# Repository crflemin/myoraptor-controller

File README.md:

# myoraptor-controller
This is the second iteration (but let's call it version 1.0) of a project combining the Raptor Reloaded 3D printed prosthetic with a MyoWare EMG sensor, a DC motor, and a Teensy 3.2. The goal is to build a prosthetic hand that responds to muscle contractions. I worked on the first iteration with an exceptional high school student who prototyped the design of the electronics control system using an Arduino Uno, breadboard, and wires. Shashi Jain designed the linear rail adapter and inspired us to combine the motor-driven Raptor with the MyoWare sensor. My contribution to this project was in pulling together the great work of these others and creating the PCB to slim down the device into something potentially wearable. I also want to thank <a href="https://github.com/wickerbox/">Wickerbox Electronics</a> for the KiCAD support and library resources!

This repository contains KiCAD design files for a PCB shield for the Teensy 3.2, as well as the Arduino code used to operate the hand.

Visit <a href="http://www.chloefleming.com/?p=90">my website</a> for pictures and more information.

## Components
1 x <a href="http://www.thingiverse.com/thing:596966">Raptor Reloaded</a> hand (scaled to 122%)</br>
1 x <a href="https://tinkercad.com/things/4MtmrpRE7Zj">linear rail adapter</a> for the Raptor Reloaded</br>
1 x <a href="https://www.adafruit.com/product/2699">MyoWare EMG sensor</a></br>
1 x <a href="https://oshpark.com/shared_projects/Pn4XONTR">MyoRaptor Controller PCB</a></br>
1 x DC motor (up to 12V)</br>

## Notes on Version 1.0
Here are some thoughts I have on the current working state of this project, and what should be done to improve future versions: </br>
* I am using a 9V battery to drive this circuit, but I am not convinced that this is moving the motor quickly enough and will likely look into other options.
* The DC motors with sufficient torque tend to be a bit bulky, and attaching them to the Raptor is not easy (this is currently being accomplished with a cheap plastic pipe clamp and a zip tie). A custom printed part should be designed to hold the motor. I'd also like to try to locate a smaller motor to power the hand.
* Right now, the PCB and linear rail adapter are sized to fit in the 122% hand. The linear rail should be made scalable with parameters and the PCB size may also need to be adjusted for smaller hands.
* The current version lacks a neat way to attach the PCB to the inside of the palm of the hand, which is another thing I'd like to improve with a printed part.

## Assembly Instructions
(in progress)

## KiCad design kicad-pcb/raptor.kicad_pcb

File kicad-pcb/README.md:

# myoraptor-controller
A PCB shield for controlling the Raptor Reloaded 3D printed prosthetic with the MyoWare EMG sensor. KiCAD library references point to <a href="https://github.com/wickerbox/">Wickerbox Electronics</a>. 
Click <a href="https://oshpark.com/shared_projects/Pn4XONTR">here</a> to order this board from OSH Park!

## Board Previews
(Courtesy of OSH Park) </br>

## Bill of Materials
|Ref|Quantity|Digikey Part Number|Manufacturer Part Number|Description|
|---|--------|-------------------|------------------------|-----------|
|U2|1|296-9911-5-ND|SN754410NE|IC HALF-H DRVR QUAD 16-DIP|
|J2, J4|2|ED10561-ND|OSTVN02A150|CONN TERM BLOCK 2.54MM 2POS PCB|
|J3|1|OSTVN03A150|OSTVN03A150|CONN TERM BLOCK 2.54MM 3POS PCB|
|D1|1|SMAJ14A-FDICT-ND|SMAJ14A-13-F|TVS DIODE 14VWM 23.2VC SMA|
|U1|1|NCP1117LPST50T3GOSCT-ND|NCP1117LPST50T3G|IC REG LDO 5V 1A SOT223|
|F1|1|MF-MSMF110/24X-2CT-ND|MF-MSMF110/24X-2|FUSE PTC RESET 1.10A SMD 1812|
|D2, D3|2|SS12-E3/61TGICT-ND|SS12-E3/61T|DIODE SCHOTTKY 20V 1A DO214AC|
|C4|1|490-1519-1-ND|GRM188R71H104KA93D|CAP CER 0.1UF 50V X7R 0603|
|C3|1|490-5307-1-ND|GRM188R71E105KA12D|CAP CER 1UF 25V X7R 0603|
|C1, C2|2|490-7202-1-ND|GRM188R61E106MA73D|CAP CER 10UF 25V X5R 0603|
|J1|1|||Teensy 3.2|

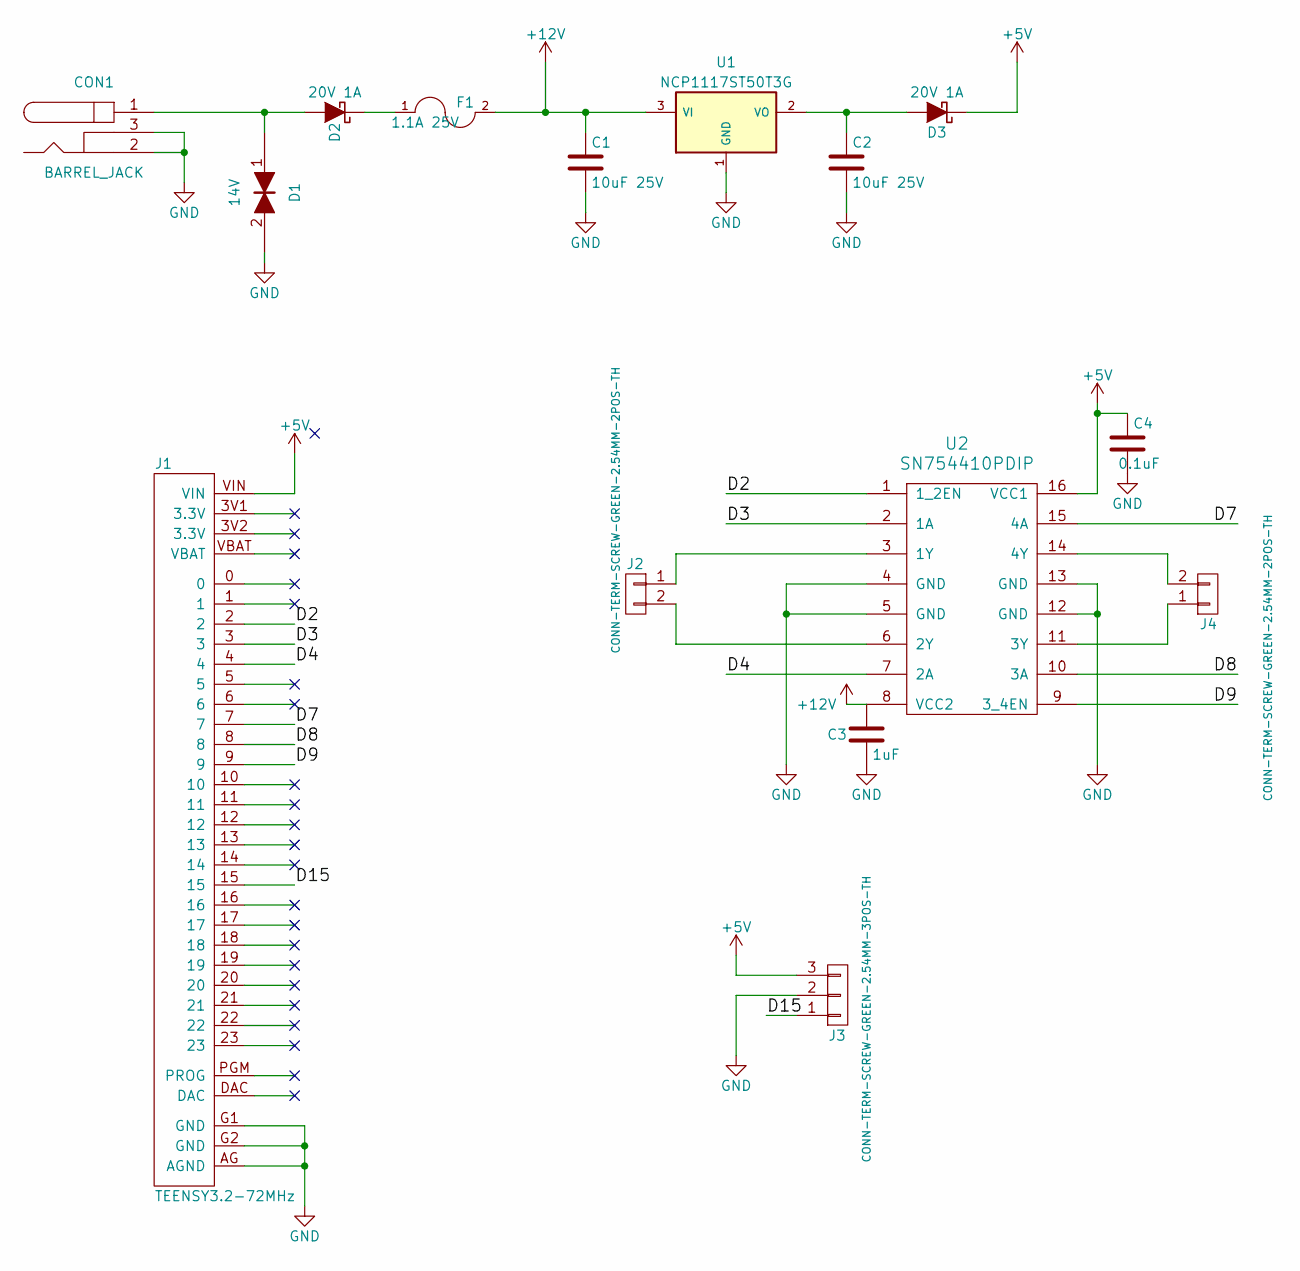
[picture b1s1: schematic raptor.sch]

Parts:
C1, C2: 10uF 25V; RLC-0603-SMD
C3: 1uF; RLC-0603-SMD
C4: 0.1uF; RLC-0603-SMD
CON1: BARREL_JACK; CONN-BARREL-JACK-2.5x5.5MM-TH
D1: 14V; DIODE-SMA
D2, D3: 20V 1A; DIODE-SMA
F1: 1.1A 25V; RLC-1812-SMD
J1: TEENSY3.2-72MHz; TEENSY-3.2-NOSILK
J2, J4: CONN-TERM-SCREW-GREEN-2.54MM-2POS-TH; CONN-ONSHORE-SCREW-GREEN-2PIN-TH
J3: CONN-TERM-SCREW-GREEN-2.54MM-3POS-TH; CONN-ONSHORE-SCREW-GREEN-3PIN-TH
U1: NCP1117ST50T3G; SOT-223
U2: SN754410PDIP; DIP-16-W7.62MM-LONGPADS

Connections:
+5V: C4.1, D3.1 (K), J1.VIN, J3.3, U2.16 (VCC1)
+12V: C1.1, C3.1, F1.2, U1.3 (VI), U2.8 (VCC2)
/D2: J1.2, U2.1 (1_2EN)
/D3: J1.3, U2.2 (1A)
/D4: J1.4, U2.7 (2A)
/D7: J1.7, U2.15 (4A)
/D8: J1.8, U2.10 (3A)
/D9: J1.9, U2.9 (3_4EN)
/D15: J1.15, J3.1
GND: C1.2, C2.2, C3.2, C4.2, CON1.2, CON1.3, D1.2, J1.AG (AGND), J1.G1 (GND), J1.G2 (GND), J3.2, U1.1 (GND), U2.4 (GND), U2.5 (GND), U2.12 (GND), U2.13 (GND)
unnamed: C2.1, D3.2 (A), U1.2 (VO)
unnamed: CON1.1, D1.1, D2.2 (A)
unnamed: D2.1 (K), F1.1
unnamed: J2.1, U2.3 (1Y)
unnamed: J2.2, U2.6 (2Y)
unnamed: J4.1, U2.11 (3Y)
unnamed: J4.2, U2.14 (4Y)

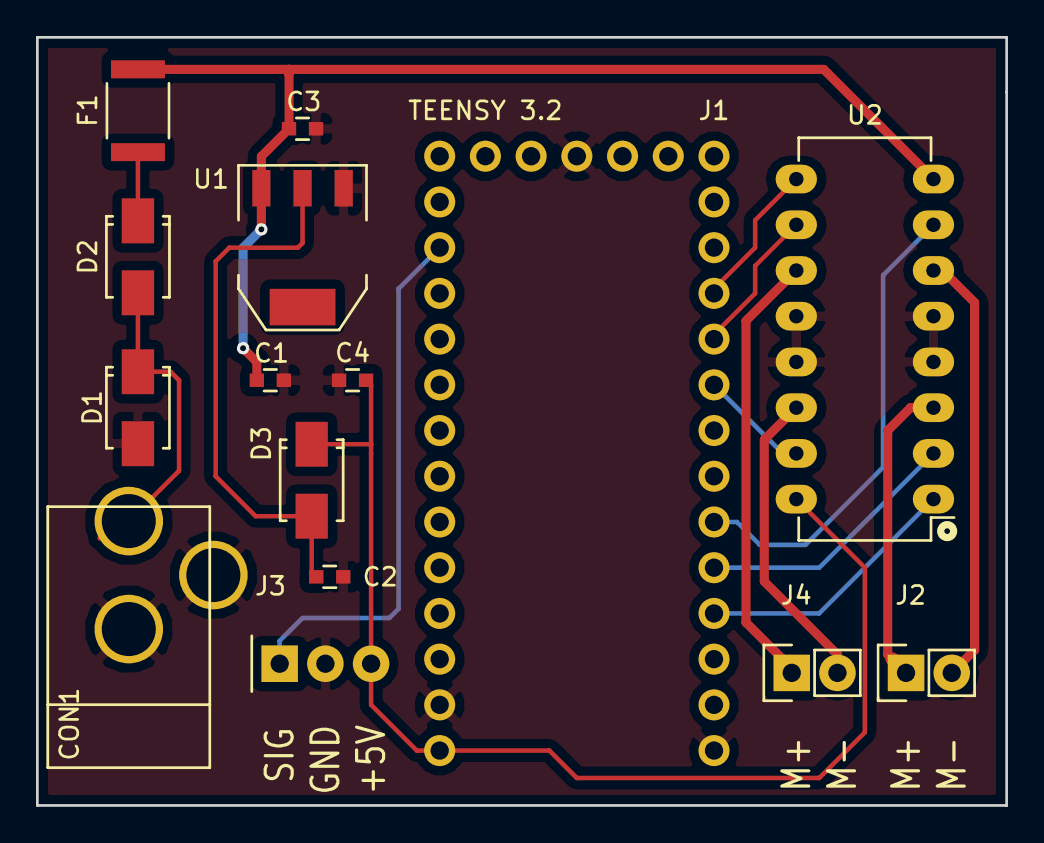
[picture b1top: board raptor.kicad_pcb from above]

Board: 2 copper layers, 53.8 x 42.7 mm, 15 parts (0 on the bottom side), 17 nets.

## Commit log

2016-08-29 Initial commit of KiCAD files + gerbers
2016-08-29 Added bill of materials and board preview images
2016-08-29 Added organized subdirectories
2016-09-02 Adding first draft of controller code for Teensy
